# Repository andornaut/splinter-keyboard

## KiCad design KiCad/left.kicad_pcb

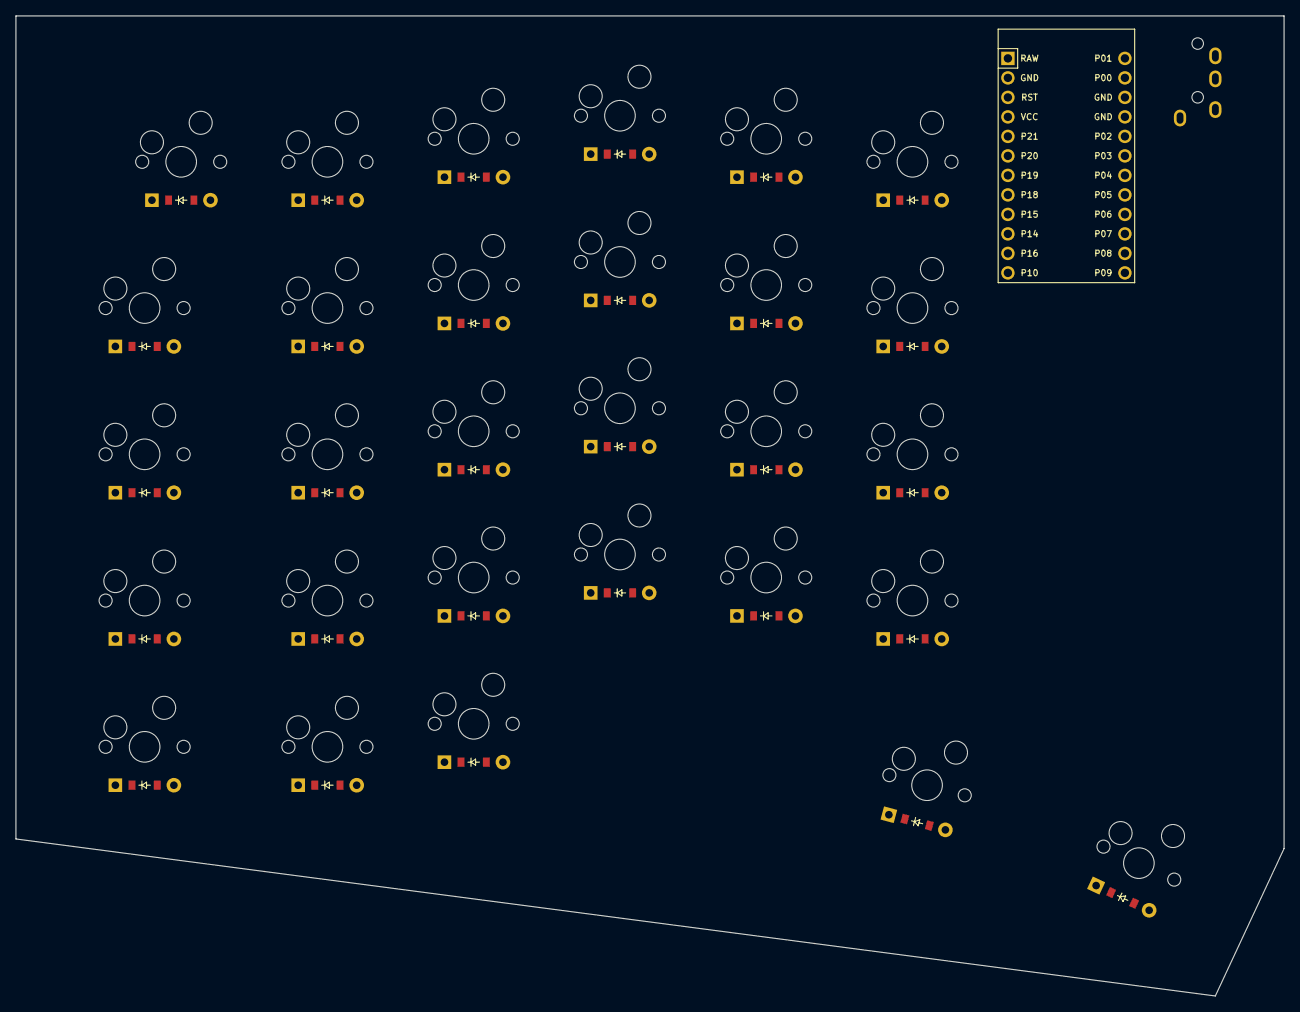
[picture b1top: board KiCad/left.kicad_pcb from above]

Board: 2 copper layers, 165.2 x 127.7 mm, 61 parts (0 on the bottom side), 45 nets, no tracks yet.

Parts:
B1: SW_TACT_ALPS_SKQGABE010
D1, D2, D3, D4, D5, D6, D7, D8, D9, D10, D11, D12, D13, D14, D15, D16, D17, D18, D19, D20, D21, D22, D23, D24, D25, D26, D27, D28, D29: ComboDiode
MCU1: ProMicro
S1, S2, S3, S4, S5, S6, S7, S8, S9, S10, S11, S12, S13, S14, S15, S16, S17, S18, S19, S20, S21, S22, S23, S24, S25, S26, S27, S28, S29: MX
TRRS1: TRRS-PJ-320A-dual

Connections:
GND: B1.1, MCU1.2, MCU1.15, MCU1.16, TRRS1.4
P4: D5.1, D10.1, D15.1, D19.1, D23.1, D27.1, MCU1.19
P5: D4.1, D9.1, D14.1, D18.1, D22.1, D26.1, MCU1.20
P6: D3.1, D8.1, D13.1, D17.1, D21.1, D25.1, MCU1.21
P7: D2.1, D7.1, D12.1, D16.1, D20.1, D24.1, MCU1.22
P8: D1.1, D6.1, D11.1, D28.1, D29.1, MCU1.23
P9: MCU1.24, S24.1, S25.1, S26.1, S27.1, S29.1
P10: MCU1.12, S20.1, S21.1, S22.1, S23.1, S28.1
P14: MCU1.10, S11.1, S12.1, S13.1, S14.1, S15.1
P15: MCU1.9, S6.1, S7.1, S8.1, S9.1, S10.1
P16: MCU1.11, S16.1, S17.1, S18.1, S19.1
P18: MCU1.8, S1.1, S2.1, S3.1, S4.1, S5.1
P20: MCU1.6, TRRS1.3
P21: MCU1.5, TRRS1.2
RST: B1.2, MCU1.3
VCC: MCU1.4, TRRS1.1
five_bottom: D24.2, S24.2
five_home: D25.2, S25.2
five_number: D27.2, S27.2
five_top: D26.2, S26.2
four_bottom: D20.2, S20.2
four_home: D21.2, S21.2
four_number: D23.2, S23.2
four_top: D22.2, S22.2
mod_meta: D29.2, S29.2
one_bottom: D7.2, S7.2
one_home: D8.2, S8.2
one_meta: D6.2, S6.2
one_number: D10.2, S10.2
one_top: D9.2, S9.2
space_meta: D28.2, S28.2
three_bottom: D16.2, S16.2
three_home: D17.2, S17.2
three_number: D19.2, S19.2
three_top: D18.2, S18.2
two_bottom: D12.2, S12.2
two_home: D13.2, S13.2
two_meta: D11.2, S11.2
two_number: D15.2, S15.2
two_top: D14.2, S14.2
zero_bottom: D2.2, S2.2
zero_home: D3.2, S3.2
zero_meta: D1.2, S1.2
zero_number: D5.2, S5.2
zero_top: D4.2, S4.2

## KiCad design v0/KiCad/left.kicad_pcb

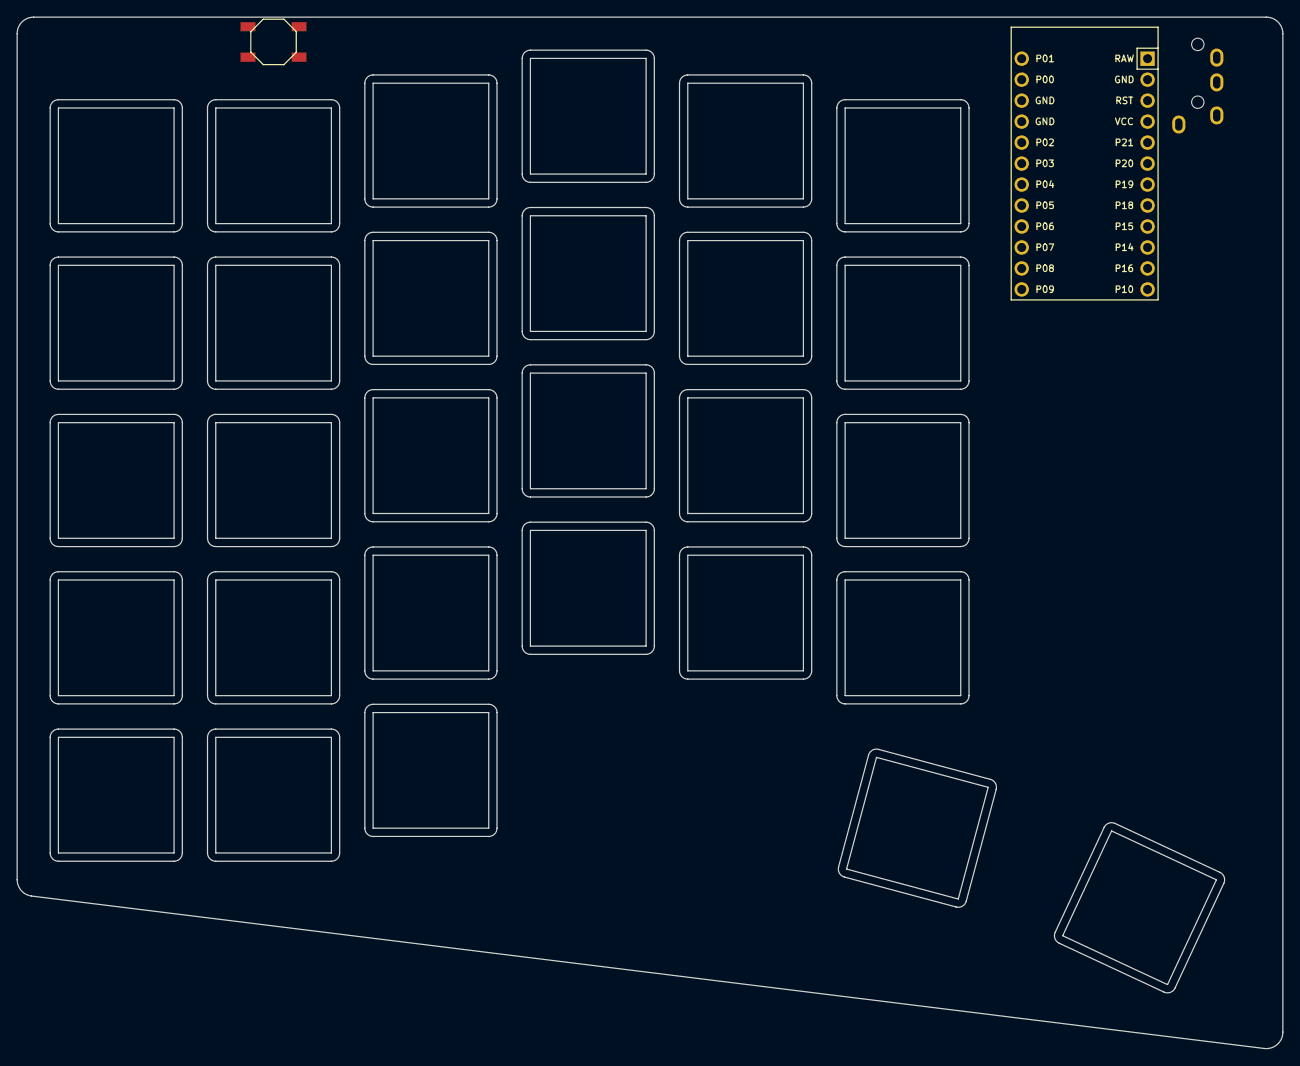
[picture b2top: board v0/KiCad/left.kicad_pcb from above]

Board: 2 copper layers, 153.3 x 124.9 mm, 3 parts (0 on the bottom side), 4 nets, no tracks yet.

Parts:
B1: SW_TACT_ALPS_SKQGABE010
MCU1: ProMicro
TRRS1: TRRS-PJ-320A-dual

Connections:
GND: B1.2, MCU1.2, MCU1.15, MCU1.16, TRRS1.1, TRRS1.2
P21: MCU1.5, TRRS1.3
RST: B1.1, MCU1.3
VCC: MCU1.4, TRRS1.4
